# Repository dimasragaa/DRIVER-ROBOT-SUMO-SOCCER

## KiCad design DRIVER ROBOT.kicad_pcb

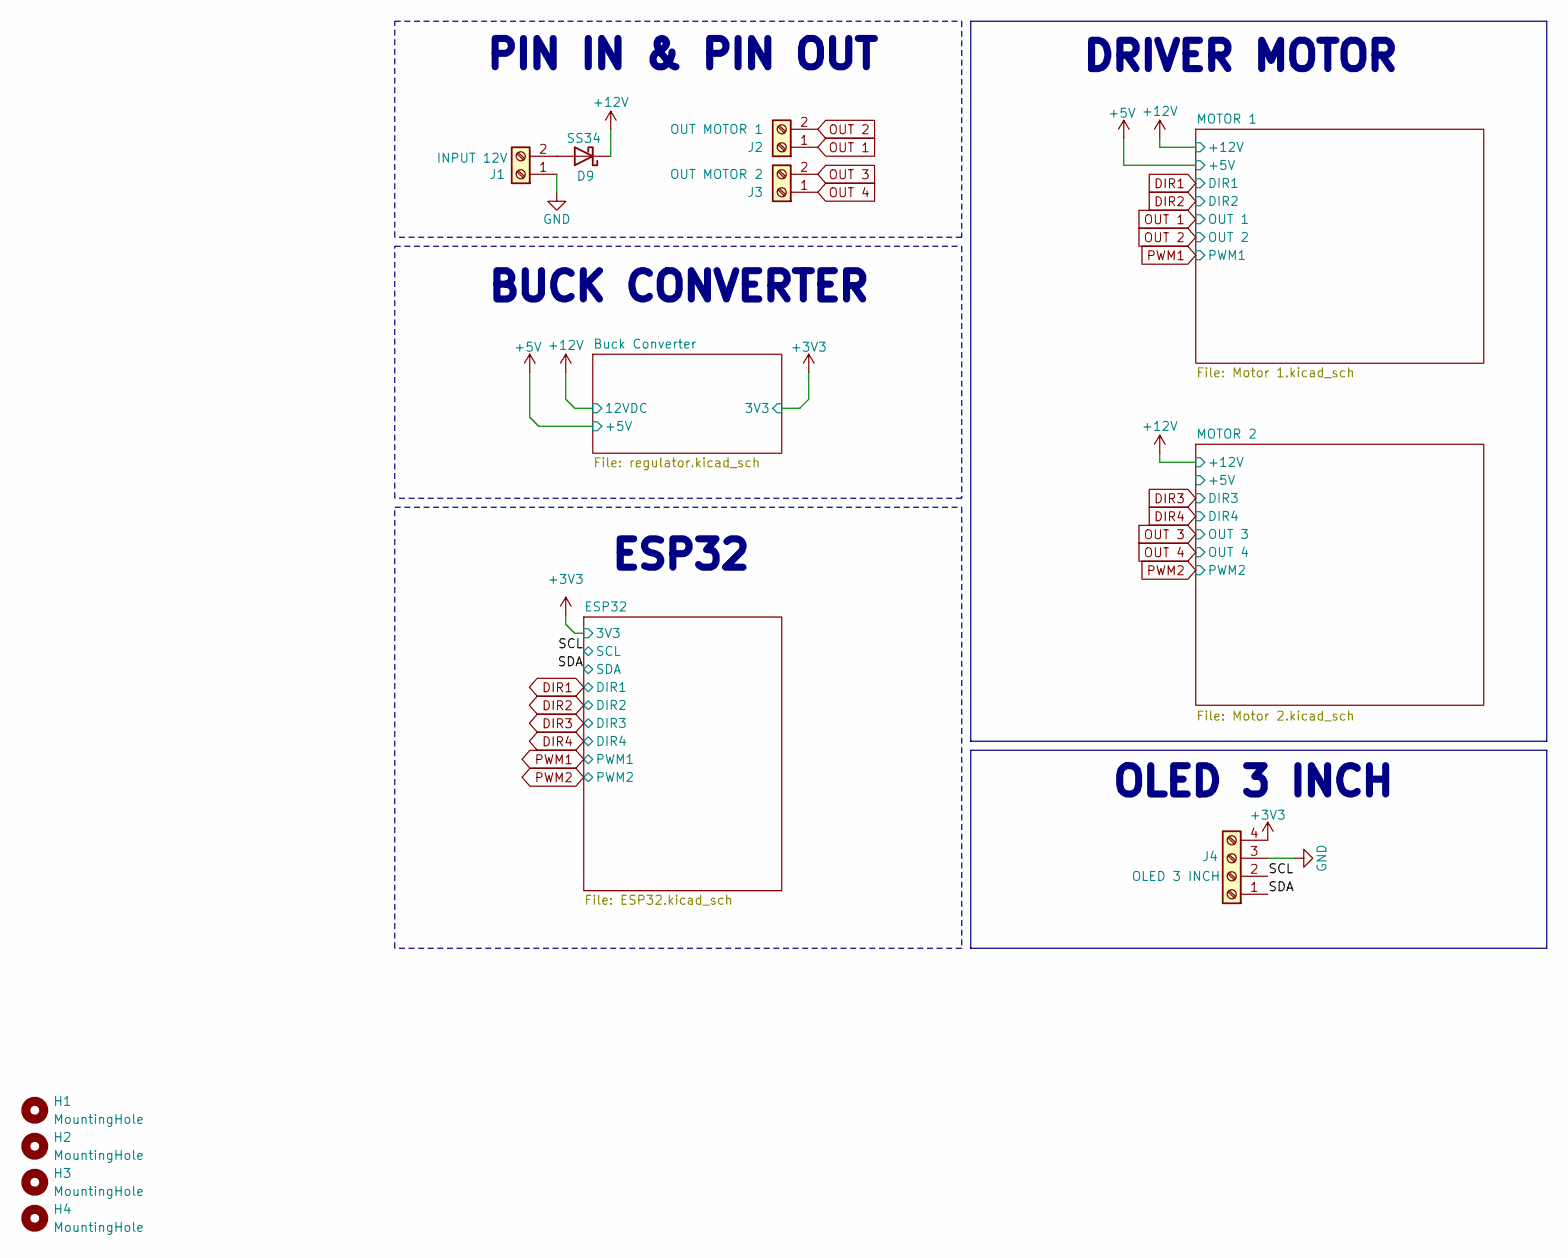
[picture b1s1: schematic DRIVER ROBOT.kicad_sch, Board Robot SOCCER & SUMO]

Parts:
D9: SS34; D_SMA
H1, H2, H3, H4: MountingHole; MountingHole_3.2mm_M3_DIN965_Pad_TopBottom
J1: INPUT 12V; TerminalBlock_Phoenix_MKDS-1,5-2_1x02_P5.00mm_Horizontal
J2: OUT MOTOR 1; TerminalBlock_Phoenix_MKDS-1,5-2_1x02_P5.00mm_Horizontal
J3: OUT MOTOR 2; TerminalBlock_Phoenix_MKDS-1,5-2_1x02_P5.00mm_Horizontal
J4: OLED 3 INCH; PinHeader_1x04_P2.54mm_Vertical

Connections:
+12V: D9.1 (K); also elsewhere on the board
/SCL: J4.2; also elsewhere on the board
/SDA: J4.1; also elsewhere on the board
GND: J1.1, J4.3; also elsewhere on the board
unnamed: D9.2 (A), J1.2
OUT 1: J2.1; also elsewhere on the board
OUT 2: J2.2; also elsewhere on the board
OUT 3: J3.2; also elsewhere on the board
OUT 4: J3.1; also elsewhere on the board

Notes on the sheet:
BUCK CONVERTER
PIN IN & PIN OUT
OLED 3 INCH
ESP32
DRIVER MOTOR

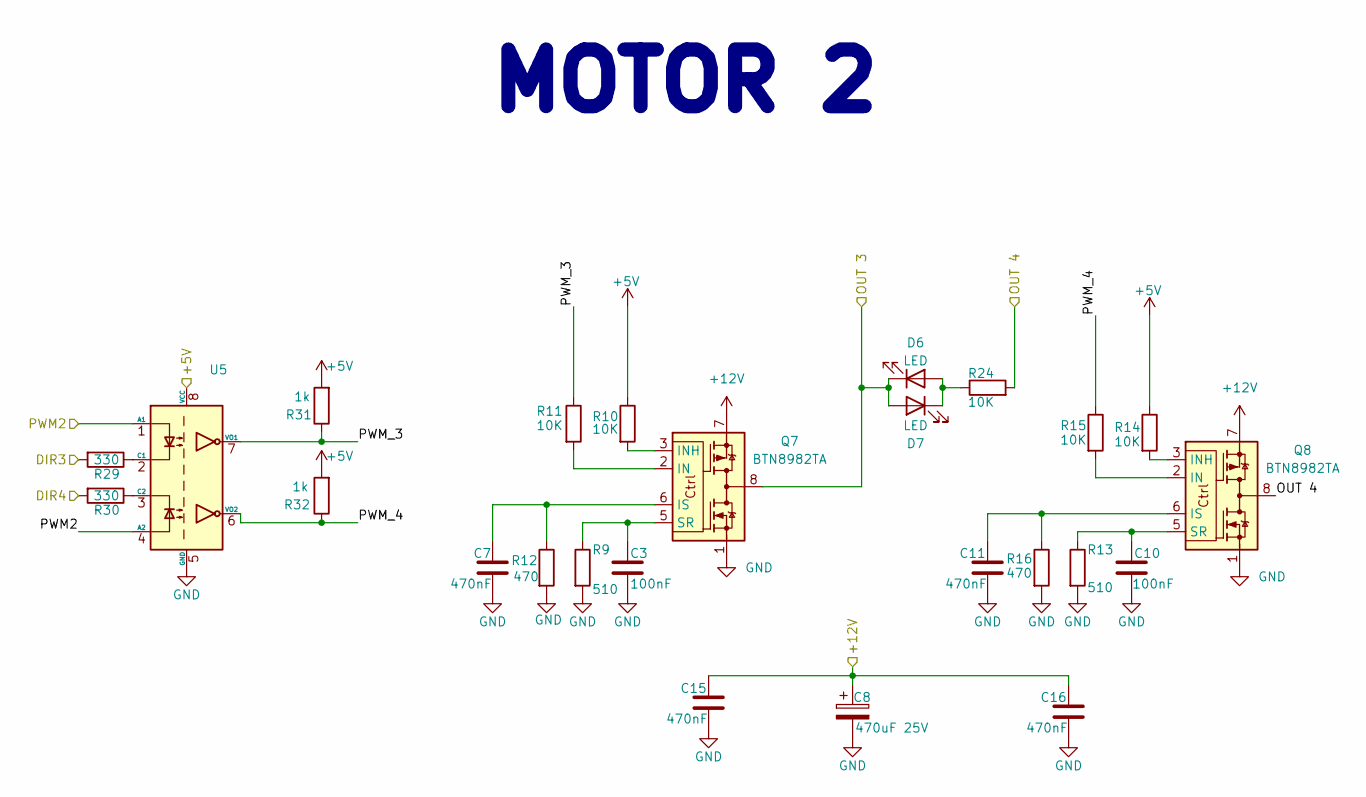
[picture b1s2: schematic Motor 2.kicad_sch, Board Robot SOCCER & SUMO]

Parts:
C3, C10: 100nF; C_0603_1608Metric_Pad1.08x0.95mm_HandSolder
C7, C11, C15, C16: 470nF; C_0603_1608Metric_Pad1.08x0.95mm_HandSolder
C8: 470uF 25V; CP_Elec_10x10.5
D6, D7: LED; LED_0805_2012Metric_Pad1.15x1.40mm_HandSolder
Q7, Q8: BTN8982TA; TO-263-7_TabPin8
R9, R13: 510; R_0603_1608Metric_Pad0.98x0.95mm_HandSolder
R10, R11, R14, R15: 10K; R_0603_1608Metric_Pad0.98x0.95mm_HandSolder
R12, R16: 470; R_0603_1608Metric_Pad0.98x0.95mm_HandSolder
R24: 10K; R_0805_2012Metric_Pad1.20x1.40mm_HandSolder
R29, R30: 330; R_0603_1608Metric_Pad0.98x0.95mm_HandSolder
R31, R32: 1k; R_0603_1608Metric_Pad0.98x0.95mm_HandSolder
U5: HCPL-2630; SOP-8_6.605x9.655mm_P2.54mm

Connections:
+5V: R10.1, R14.1, R31.2, R32.2, U5.8 (VCC); also elsewhere on the board
+12V: C8.1, C15.1, C16.1, Q7.7, Q8.7; also elsewhere on the board
/MOTOR 2/PWM_3: R11.1, R31.1, U5.7 (VO1)
/MOTOR 2/PWM_4: R15.1, R32.1, U5.6 (VO2)
DIR3: R29.2; also elsewhere on the board
DIR4: R30.2; also elsewhere on the board
GND: C3.2, C7.2, C8.2, C10.2, C11.2, C15.2, C16.2, Q7.1, Q8.1, R9.2, R12.2, R13.2, R16.2, U5.5 (GND); also elsewhere on the board
unnamed: D6.2 (A), D7.1 (K), R24.1
unnamed: Q7.2 (IN), R11.2
unnamed: Q7.3 (INH), R10.2
unnamed: C7.1, Q7.6 (IS), R12.1
unnamed: C3.1, Q7.5 (SR), R9.1
unnamed: Q8.2 (IN), R15.2
unnamed: Q8.3 (INH), R14.2
unnamed: C11.1, Q8.6 (IS), R16.1
unnamed: C10.1, Q8.5 (SR), R13.1
unnamed: R29.1, U5.2 (C1)
unnamed: R30.1, U5.3 (C2)
OUT 3: D6.1 (K), D7.2 (A), Q7.4, Q7.8; also elsewhere on the board
OUT 4: Q8.4, Q8.8, R24.2; also elsewhere on the board
PWM2: U5.1 (A1), U5.4 (A2); also elsewhere on the board

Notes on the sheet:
MOTOR 2

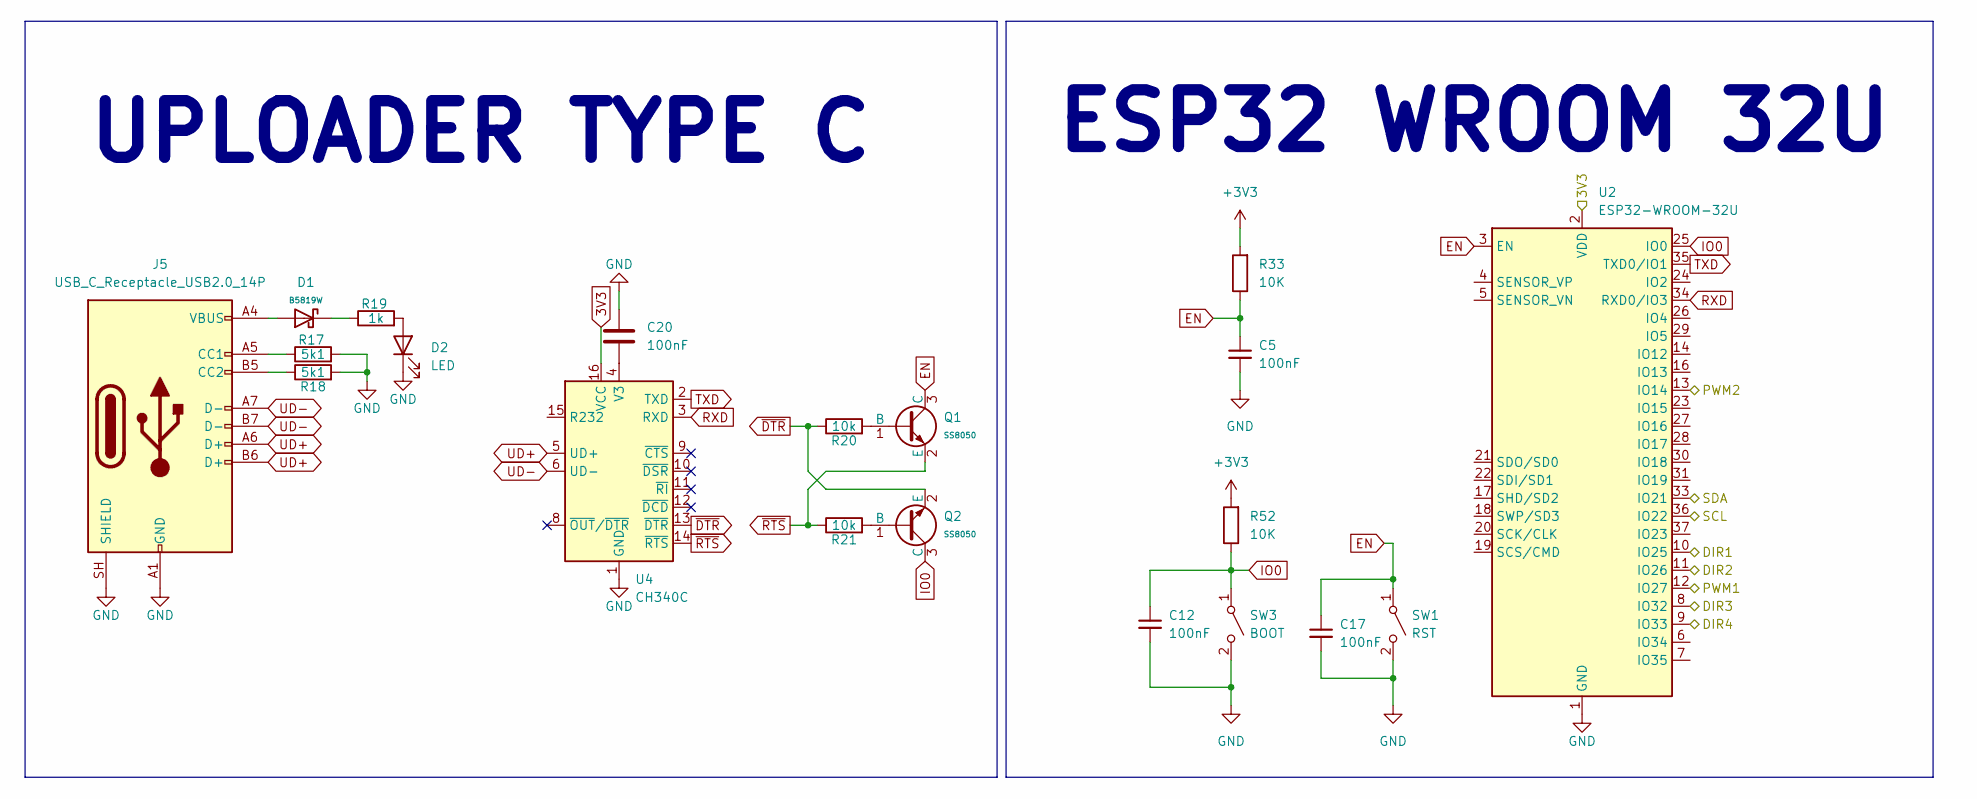
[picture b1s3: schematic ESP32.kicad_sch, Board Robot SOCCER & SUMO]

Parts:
C5, C12, C17: 100nF; C_0603_1608Metric_Pad1.08x0.95mm_HandSolder; LCSC C1711
C20: 100nF; C_0603_1608Metric_Pad1.08x0.95mm_HandSolder
D1: B5819W; Nexperia_CFP3_SOD-123W; Forward Voltage (Vf@If) 900mV@3A; Reverse Voltage (Vr) 40V; Part B5819W; LCSC C64885
D2: LED; LED_0603_1608Metric_Pad1.05x0.95mm_HandSolder
J5: USB_C_Receptacle_USB2.0_14P; USB_C_Plug_ShenzhenJingTuoJin_918-118A2021Y40002_Vertical
Q1, Q2: SS8050; SOT-23_Handsoldering; Part SS8050; LCSC C431710
R17, R18: 5k1; R_0603_1608Metric_Pad0.98x0.95mm_HandSolder
R19: 1k; R_0603_1608Metric_Pad0.98x0.95mm_HandSolder
R20, R21: 10k; R_0603_1608Metric_Pad0.98x0.95mm_HandSolder
R33, R52: 10K; R_0603_1608Metric_Pad0.98x0.95mm_HandSolder; LCSC C17414
SW1: RST; SW_SPST_TS-1088-xR025; LCSC C231329
SW3: BOOT; SW_SPST_TS-1088-xR025; LCSC C231329
U2: ESP32-WROOM-32U
U4: CH340C; SOIC-16_3.9x9.9mm_P1.27mm

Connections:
/SCL: U2.36 (IO22); also elsewhere on the board
/SDA: U2.33 (IO21); also elsewhere on the board
DIR1: U2.10 (IO25); also elsewhere on the board
DIR2: U2.11 (IO26); also elsewhere on the board
DIR3: U2.8 (IO32); also elsewhere on the board
DIR4: U2.9 (IO33); also elsewhere on the board
EN: C5.1, C17.1, Q1.3 (C), R33.1, SW1.1 (A), U2.3 (EN)
GND: C5.2, C12.2, C17.2, C20.1, D2.1 (K), J5.A1 (GND), J5.A12 (GND), J5.B1 (GND), J5.B12 (GND), J5.SH (SHIELD), R17.2, R18.2, SW1.2 (B), SW3.2 (B), U2.1 (GND), U2.15 (GND), U2.38 (GND), U2.39 (GND), U4.1 (GND); also elsewhere on the board
IO0: C12.1, Q2.3 (C), R52.1, SW3.1 (A), U2.25 (IO0)
unnamed: D1.1, R19.1
unnamed: D1.2, J5.A4 (VBUS), J5.A9 (VBUS), J5.B4 (VBUS), J5.B9 (VBUS)
unnamed: D2.2 (A), R19.2
unnamed: J5.A5 (CC1), R17.1
unnamed: J5.B5 (CC2), R18.1
unnamed: Q1.1 (B), R20.2
unnamed: Q2.1 (B), R21.2
unnamed: C20.2, U4.4 (V3)
PWM1: U2.12 (IO27); also elsewhere on the board
PWM2: U2.13 (IO14); also elsewhere on the board
RXD: U2.34 (RXD0/IO3), U4.3 (RXD)
TXD: U2.35 (TXD0/IO1), U4.2 (TXD)
UD+: J5.A6 (D+), J5.B6 (D+), U4.5 (UD+)
UD-: J5.A7 (D-), J5.B7 (D-), U4.6 (UD-)
~DTR: Q2.2 (E), R20.1, U4.13 (~DTR)
~RTS: Q1.2 (E), R21.1, U4.14 (~RTS)

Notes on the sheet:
ESP32 WROOM 32U
UPLOADER TYPE C

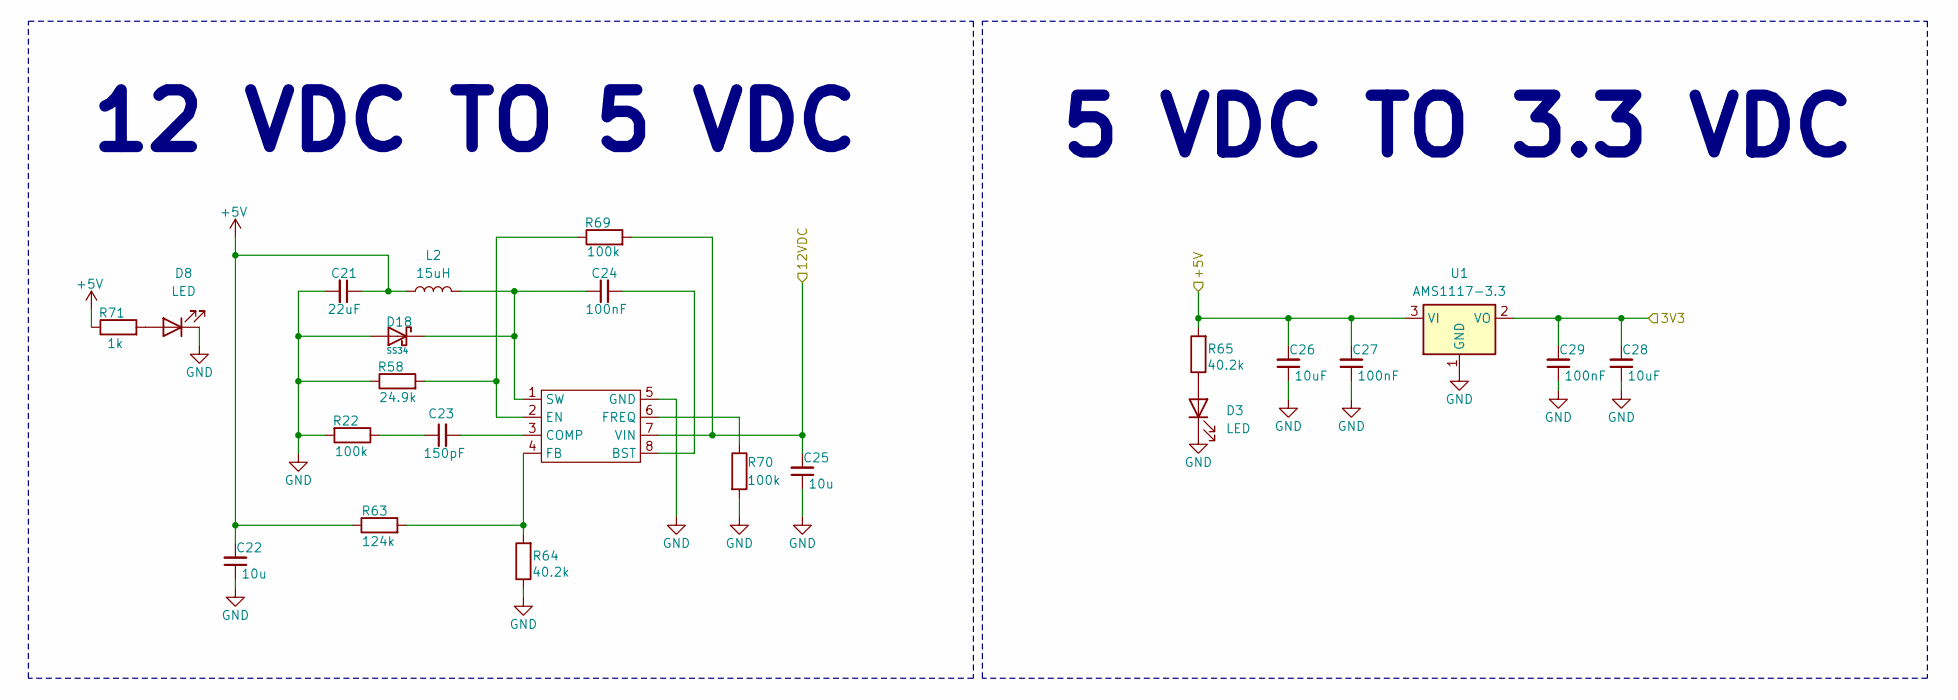
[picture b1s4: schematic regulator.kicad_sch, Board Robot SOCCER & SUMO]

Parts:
C21: 22uF; C_0805_2012Metric; LCSC C1711
C22, C25: 10u; C_0805_2012Metric; LCSC C1711
C23: 150pF; C_0603_1608Metric_Pad1.08x0.95mm_HandSolder; LCSC C1711
C24, C27, C29: 100nF; C_0805_2012Metric_Pad1.18x1.45mm_HandSolder; LCSC C1711
C26, C28: 10uF; C_0805_2012Metric; LCSC C1711
D3, D8: LED; LED_0603_1608Metric_Pad1.05x0.95mm_HandSolder
D18: SS34; D_SMA; Forward Voltage (Vf@If) 550mV@3A; Reverse Voltage (Vr) 40V; Part SS34; LCSC C8678
L2: 15uH; L_Chilisin_BMRx00060630
MP1584: SOIC-8-1EP_3.9x4.9mm_P1.27mm_EP2.29x3mm
R22: 100k; R_0603_1608Metric_Pad0.98x0.95mm_HandSolder; LCSC C17540
R58: 24.9k; R_0603_1608Metric_Pad0.98x0.95mm_HandSolder; LCSC C17540
R63: 124k; R_0603_1608Metric_Pad0.98x0.95mm_HandSolder; LCSC C17540
R64: 40.2k; R_0603_1608Metric_Pad0.98x0.95mm_HandSolder; LCSC C17540
R65: 40.2k; R_0805_2012Metric_Pad1.20x1.40mm_HandSolder; LCSC C17540
R69, R70: 100k; R_0805_2012Metric_Pad1.20x1.40mm_HandSolder; LCSC C17540
R71: 1k; R_0603_1608Metric_Pad0.98x0.95mm_HandSolder; LCSC C17540
U1: AMS1117-3.3; SOT-223-3_TabPin2

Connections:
+5V: C21.1, C22.2, C26.2, C27.2, L2.1, R63.1, R65.2, R71.1, U1.3 (VI); also elsewhere on the board
+12V: C25.2, MP1584.7 (VIN), R69.2; also elsewhere on the board
GND: C21.2, C22.1, C25.1, C26.1, C27.1, C28.1, C29.1, D3.1 (K), D8.1 (K), D18.2, MP1584.5 (GND), R22.2, R58.1, R64.1, R70.2, U1.1 (GND); also elsewhere on the board
unnamed: C23.1, R22.1
unnamed: D3.2 (A), R65.1
unnamed: D8.2 (A), R71.2
unnamed: C24.2, MP1584.8 (BST)
unnamed: C23.2, MP1584.3 (COMP)
unnamed: MP1584.2 (EN), R58.2, R69.1
unnamed: MP1584.4 (FB), R63.2, R64.2
unnamed: MP1584.6 (FREQ), R70.1
unnamed: C24.1, D18.1, L2.2, MP1584.1 (SW)

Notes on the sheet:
12 VDC TO 5 VDC
5 VDC TO 3.3 VDC

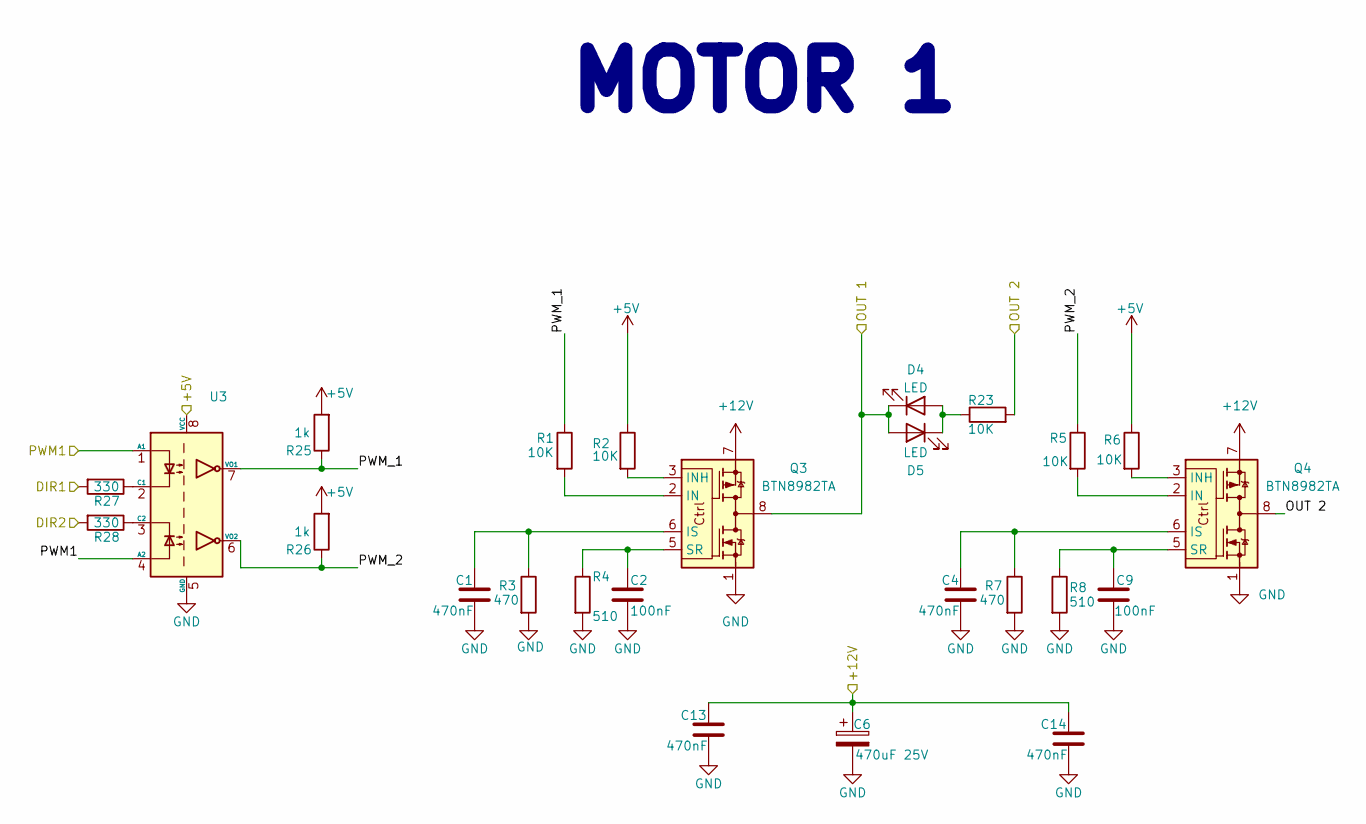
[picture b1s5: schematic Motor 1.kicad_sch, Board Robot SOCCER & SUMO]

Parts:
C1, C4, C13, C14: 470nF; C_0603_1608Metric_Pad1.08x0.95mm_HandSolder
C2, C9: 100nF; C_0603_1608Metric_Pad1.08x0.95mm_HandSolder
C6: 470uF 25V; CP_Elec_10x10.5
D4, D5: LED; LED_0805_2012Metric_Pad1.15x1.40mm_HandSolder
Q3, Q4: BTN8982TA; TO-263-7_TabPin8
R1, R2, R5, R6: 10K; R_0603_1608Metric_Pad0.98x0.95mm_HandSolder
R3, R7: 470; R_0603_1608Metric_Pad0.98x0.95mm_HandSolder
R4, R8: 510; R_0603_1608Metric_Pad0.98x0.95mm_HandSolder
R23: 10K; R_0805_2012Metric_Pad1.20x1.40mm_HandSolder
R25, R26: 1k; R_0603_1608Metric_Pad0.98x0.95mm_HandSolder
R27, R28: 330; R_0603_1608Metric_Pad0.98x0.95mm_HandSolder
U3: HCPL-2630; SOP-8_6.605x9.655mm_P2.54mm

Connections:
+5V: R2.1, R6.1, R25.2, R26.2, U3.8 (VCC); also elsewhere on the board
+12V: C6.1, C13.1, C14.1, Q3.7, Q4.7; also elsewhere on the board
/MOTOR 1/PWM_1: R1.1, R25.1, U3.7 (VO1)
/MOTOR 1/PWM_2: R5.1, R26.1, U3.6 (VO2)
DIR1: R27.2; also elsewhere on the board
DIR2: R28.2; also elsewhere on the board
GND: C1.2, C2.2, C4.2, C6.2, C9.2, C13.2, C14.2, Q3.1, Q4.1, R3.2, R4.2, R7.2, R8.2, U3.5 (GND); also elsewhere on the board
unnamed: D4.2 (A), D5.1 (K), R23.1
unnamed: Q3.2 (IN), R1.2
unnamed: Q3.3 (INH), R2.2
unnamed: C1.1, Q3.6 (IS), R3.1
unnamed: C2.1, Q3.5 (SR), R4.1
unnamed: Q4.2 (IN), R5.2
unnamed: Q4.3 (INH), R6.2
unnamed: C4.1, Q4.6 (IS), R7.1
unnamed: C9.1, Q4.5 (SR), R8.1
unnamed: R27.1, U3.2 (C1)
unnamed: R28.1, U3.3 (C2)
OUT 1: D4.1 (K), D5.2 (A), Q3.4, Q3.8; also elsewhere on the board
OUT 2: Q4.4, Q4.8, R23.2; also elsewhere on the board
PWM1: U3.1 (A1), U3.4 (A2); also elsewhere on the board

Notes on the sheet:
MOTOR 1

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
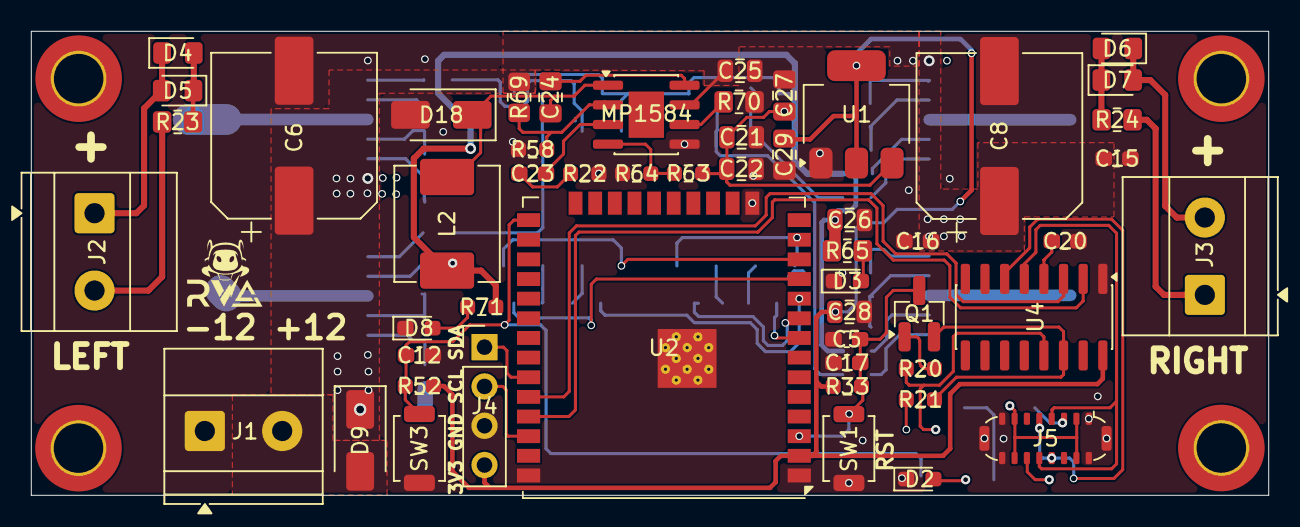
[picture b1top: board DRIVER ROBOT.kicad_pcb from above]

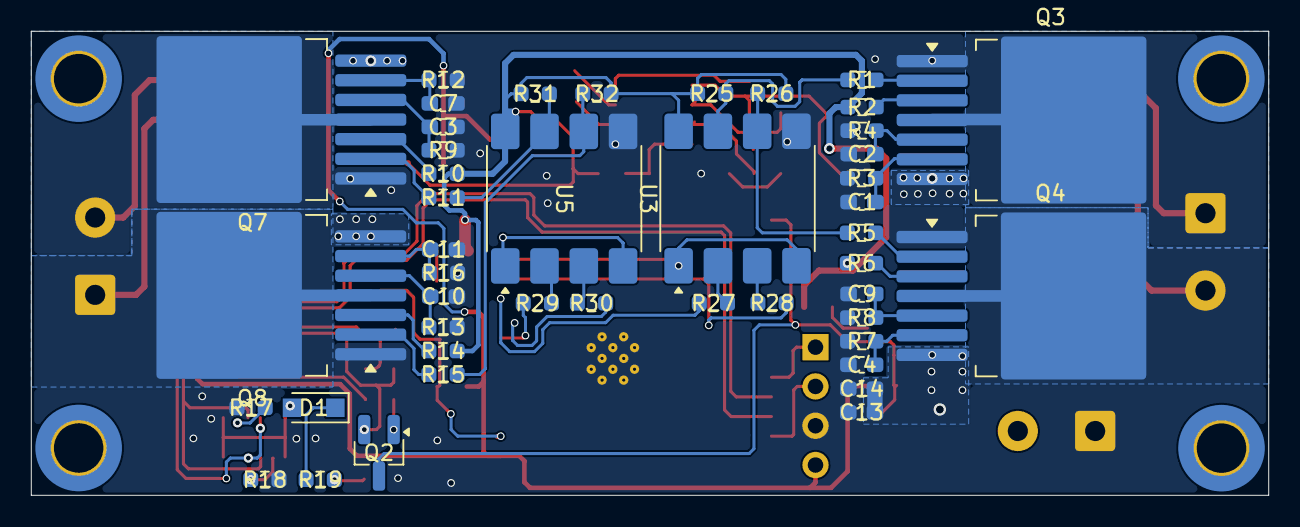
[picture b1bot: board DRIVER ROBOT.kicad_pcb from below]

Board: 2 copper layers, 80.0 x 30.0 mm, 102 parts (45 on the bottom side), 68 nets.

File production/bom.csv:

Designator,Footprint,Quantity,Value,LCSC Part #
"C1, C11, C13, C14, C15, C16, C4, C7",0603,8,470nF,
"C10, C2, C20, C3, C9",0603,5,100nF,
"C12, C17, C5",0603,3,100nF,C1711
C21,0805,1,22uF,C1711
"C22, C25",0805,2,10u,C1711
C23,0603,1,150pF,C1711
"C24, C27, C29",0805,3,100nF,C1711
"C26, C28",0805,2,10uF,C1711
"C6, C8",CP_Elec_10x10.5,2,470uF 25V,
D1,Nexperia_CFP3_SOD-123W,1,B5819W,C64885
D18,D_SMA,1,SS34,C8678
"D2, D3, D8",0603,3,LED,
"D4, D5, D6, D7",0805,4,LED,
D9,D_SMA,1,SS34,
J1,"TerminalBlock_Phoenix_MKDS-1,5-2_1x02_P5.00mm_Horizontal",1,INPUT 12V,
J2,"TerminalBlock_Phoenix_MKDS-1,5-2_1x02_P5.00mm_Horizontal",1,OUT MOTOR 1,
J3,"TerminalBlock_Phoenix_MKDS-1,5-2_1x02_P5.00mm_Horizontal",1,OUT MOTOR 2,
J4,PinHeader_1x04_P2.54mm_Vertical,1,OLED 3 INCH,
J5,USB_C_Plug_ShenzhenJingTuoJin_918-118A2021Y40002_Vertical,1,USB_C_Receptacle_USB2.0_14P,
L2,L_Chilisin_BMRx00060630,1,15uH,
MP1584,SOIC-8-1EP_3.9x4.9mm_P1.27mm_EP2.29x3mm,1,~,
"Q1, Q2",SOT-23_Handsoldering,2,SS8050,C431710
"Q3, Q4, Q7, Q8",TO-263-7_TabPin8,4,BTN8982TA,
"R1, R10, R11, R14, R15, R2, R20, R21, R5, R6",0603,10,10K,
"R12, R16, R3, R7",0603,4,470,
"R13, R4, R8, R9",0603,4,510,
"R17, R18",0603,2,5k1,
"R19, R25, R26, R31, R32",0603,5,1k,
R22,0603,1,100k,C17540
"R23, R24",0805,2,10K,
"R27, R28, R29, R30",0603,4,330,
"R33, R52",0603,2,10K,C17414
R58,0603,1,24.9k,C17540
R63,0603,1,124k,C17540
R64,0603,1,40.2k,C17540
R65,0805,1,40.2k,C17540
"R69, R70",0805,2,100k,C17540
R71,0603,1,1k,C17540
SW1,SW_SPST_TS-1088-xR025,1,RST,C231329
SW3,SW_SPST_TS-1088-xR025,1,BOOT,C231329
U1,SOT-223-3_TabPin2,1,AMS1117-3.3,
U2,ESP32-WROOM-32U,1,ESP32-WROOM-32U,
"U3, U5",SOP-8_6.605x9.655mm_P2.54mm,2,HCPL-2630,
U4,SOIC-16_3.9x9.9mm_P1.27mm,1,CH340C,
